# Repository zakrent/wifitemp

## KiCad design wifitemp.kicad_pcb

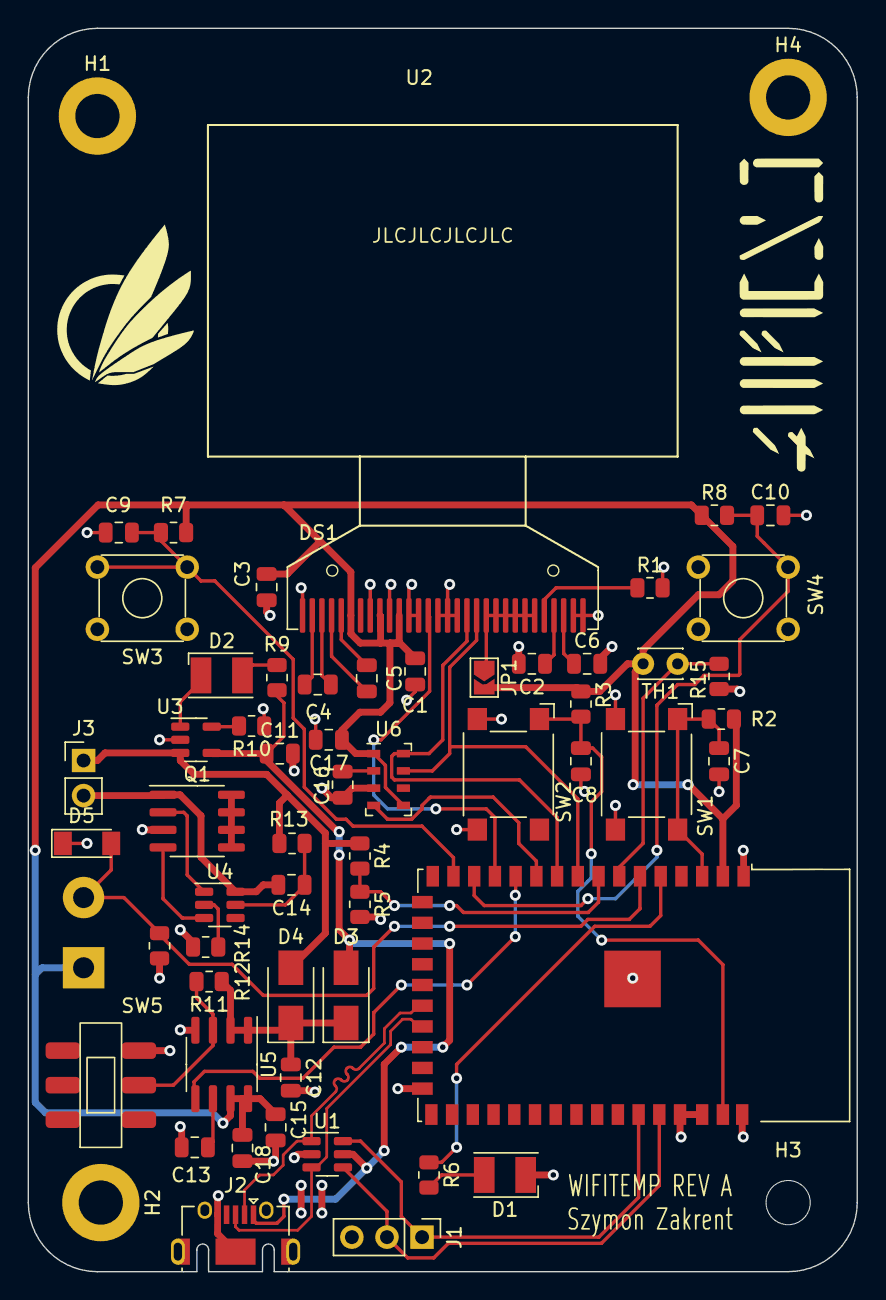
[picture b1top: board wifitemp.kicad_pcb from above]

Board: 2 copper layers, 60.0 x 90.0 mm, 61 parts (1 on the bottom side), 43 nets.

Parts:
C1, C2, C3, C4, C5, C6, C11, C12, C15, C16, C18: 1u; C_0805_2012Metric
C7, C8, C9, C10, C17: 100n; C_0805_2012Metric
C13: DNP; C_0805_2012Metric
C14: C; C_0805_2012Metric
D1, D2: LED; LED_PLCC-2
D3, D4: D_Schottky; D_SMA
D5: D; D_MiniMELF
DS1: REX012864LYAP3N00000
H1, H2, H4: MountingHole_Pad; MountingHole_3.2mm_M3_DIN965_Pad
H3: MountingHole_Pad; MountingHole_3.2mm_M3_DIN965
J1: Conn_01x03; PinHeader_1x03_P2.54mm_Vertical
J2: USB_OTG; USB_Micro-AB_Molex_47590-0001
J3: Conn_01x02; PinHeader_1x02_P2.54mm_Vertical
J4: Conn_01x02; TerminalBlock_bornier-2_P5.08mm
JP1: SJ_2; SolderJumper-2_P1.3mm_Open_TrianglePad1.0x1.5mm
Q1: Q_Dual_NMOS; SOIC-8_3.9x4.9mm_P1.27mm
R1: 310k; R_0805_2012Metric
R2, R3, R7, R8, R11: 1k; R_0805_2012Metric
R4, R5: 100k; R_0805_2012Metric
R6, R9, R10, R12, R13, R14, R15: R; R_0805_2012Metric
SW1, SW2: SW_PUSH; SW_SPST_Omron_B3FS-100xP
SW3, SW4: SW_PUSH_L; SW_TH_Tactile_Omron_B3F-10xx
SW5: SW_DPDT_x2; JS202011SCQN
TH1: Thermistor; C_Disc_D3.0mm_W2.0mm_P2.50mm
U1: SRV05-4; SOT-23-6
U2: ESP32-S2-WROVER
U3: LTC4054ES5-4.2; TSOT-23-5
U4: AP9101CK6; SOT-23-6
U5: MCP1726-3302E; SOIC-8_3.9x4.9mm_P1.27mm
U6: MPL115A2; LGA-8_3x5mm_P1.25mm

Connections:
+3V3: C1.1, C3.1, C15.1, C17.1, C18.1, DS1.6 (VDD2), DS1.9 (VDD1), DS1.11 (IM1), J4.1, JP1.2 (B), R2.1, R3.1, R7.1, R8.1, TH1.1, U2.2 (3V3), U5.7 (Vout), U5.8 (Vout), U6.1 (VDD), U6.5 (~RST)
+5V: C11.1, D3.2 (A), J2.1 (VBUS), R9.1, U1.5 (VP), U3.4 (VCC)
+BATT: D4.2 (A), J3.1, R4.1, R13.2, U3.3 (BAT)
-BATT: C14.2, J3.2, Q1.1 (S), U4.6 (VSS)
/MCU/EN: C8.1, R3.2, SW2.1, SW2.2, U2.41 (EN)
/MCU/IO0: C7.1, R2.2, SW1.1, SW1.2, U2.3 (IO00)
/MCU/RXD: J1.2, U1.4 (IO3), U2.38 (RXD0)
/MCU/TXD: J1.1, U1.6 (IO4), U2.37 (TXD0)
/MCU/USB_D+: J2.3 (D+), U1.3 (IO2), U2.23 (USB_D+)
/MCU/USB_D-: J2.2 (D-), U1.1 (IO1), U2.22 (USB_D-)
/MCU/V_BAT_2: R4.2, R5.1, U2.8 (IO05)
BUT0: C9.1, R7.2, SW3.1, SW3.2, U2.15 (IO12)
BUT1: C10.1, R8.2, SW4.1, SW4.2, U2.14 (IO11)
GND: C1.2, C2.2, C3.2, C6.2, C7.2, C8.2, C9.2, C10.2, C11.2, C12.2, C13.1, C15.2, C16.2, C17.2, C18.2, D1.1 (K), D5.1 (K), DS1.1 (NC(GND)), DS1.8 (VSS), DS1.10 (IM0), DS1.12 (IM2), DS1.13 (~CS), DS1.15 (A0), DS1.16 (~WR), DS1.17 (~RD), DS1.29 (VSL), DS1.30 (NC(GND)), H1.1, H2.1, H4.1, J1.3, J2.5 (GND), J2.6 (Shield), Q1.3 (S), R1.2, R5.2, R10.1, R12.1, R14.2, R15.2, SW1.3 (K), SW1.4 (A), SW2.3 (K), SW2.4 (A), SW3.3 (K), SW3.4 (A), SW4.3 (K), SW4.4 (A), SW5.3 (C), U1.2 (VN), U2.1 (GND), U2.26 (GND), U2.39 (IO45), U2.40 (IO46), U2.42 (GND), U2.43 (GND), U3.2 (GND), U5.4 (GND), U6.3 (GND)
unnamed: C2.1, DS1.27 (VCOMH)
unnamed: C4.1, DS1.2 (C1N)
unnamed: C4.2, DS1.3 (C1P)
unnamed: C5.1, DS1.4 (C2P)
unnamed: C5.2, DS1.5 (C2N)
unnamed: C6.1, DS1.28 (VPP)
unnamed: C12.1, D3.1 (K), D4.1 (K), R11.1, U5.1 (Vin), U5.2 (Vin)
unnamed: C13.2, U5.6 (Cdelay)
unnamed: C14.1, R13.1, U4.5 (VDD)
unnamed: C16.1, U6.2 (CAP)
unnamed: D1.2 (A), R6.2
unnamed: D2.1 (K), U3.1 (~CHRG)
unnamed: D2.2 (A), R9.2
unnamed: DS1.20 (D2), DS1.21 (D3), DS1.22 (D4), DS1.23 (D5), DS1.24 (D6), DS1.25 (D7), JP1.1 (A)
unnamed: DS1.26 (IREF), R1.1
unnamed: Q1.2 (G), U4.1 (DO)
unnamed: Q1.4 (G), U4.3 (CO)
unnamed: Q1.5 (D), Q1.6 (D), Q1.7 (D), Q1.8 (D)
unnamed: R6.1, U2.5 (IO02)
unnamed: R10.2, U3.5 (PROG)
unnamed: R11.2, SW5.2 (B), U5.3 (~SHDN)
unnamed: R12.2, U4.2 (VM)
PWRGD: U2.12 (IO09), U5.5 (PWRGD)
SCL: DS1.18 (D0), U2.10 (IO07), U6.8 (SCL)
SDA: DS1.19 (D1), U2.9 (IO06), U6.7 (SDA)
TEMP_INSIDE: R15.1, TH1.2, U2.7 (IO04)
TEMP_OUTSIDE: D5.2 (A), J4.2, R14.1, U2.6 (IO03)
~DS_RES: DS1.14 (~RES), U2.13 (IO10)
~PRES_SHDN: U2.11 (IO08), U6.4 (~SHDN)
